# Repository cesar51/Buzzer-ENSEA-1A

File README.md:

# Buzzer-ENSEA-1A
Projet de buzzers connectés pour jeux et quiz

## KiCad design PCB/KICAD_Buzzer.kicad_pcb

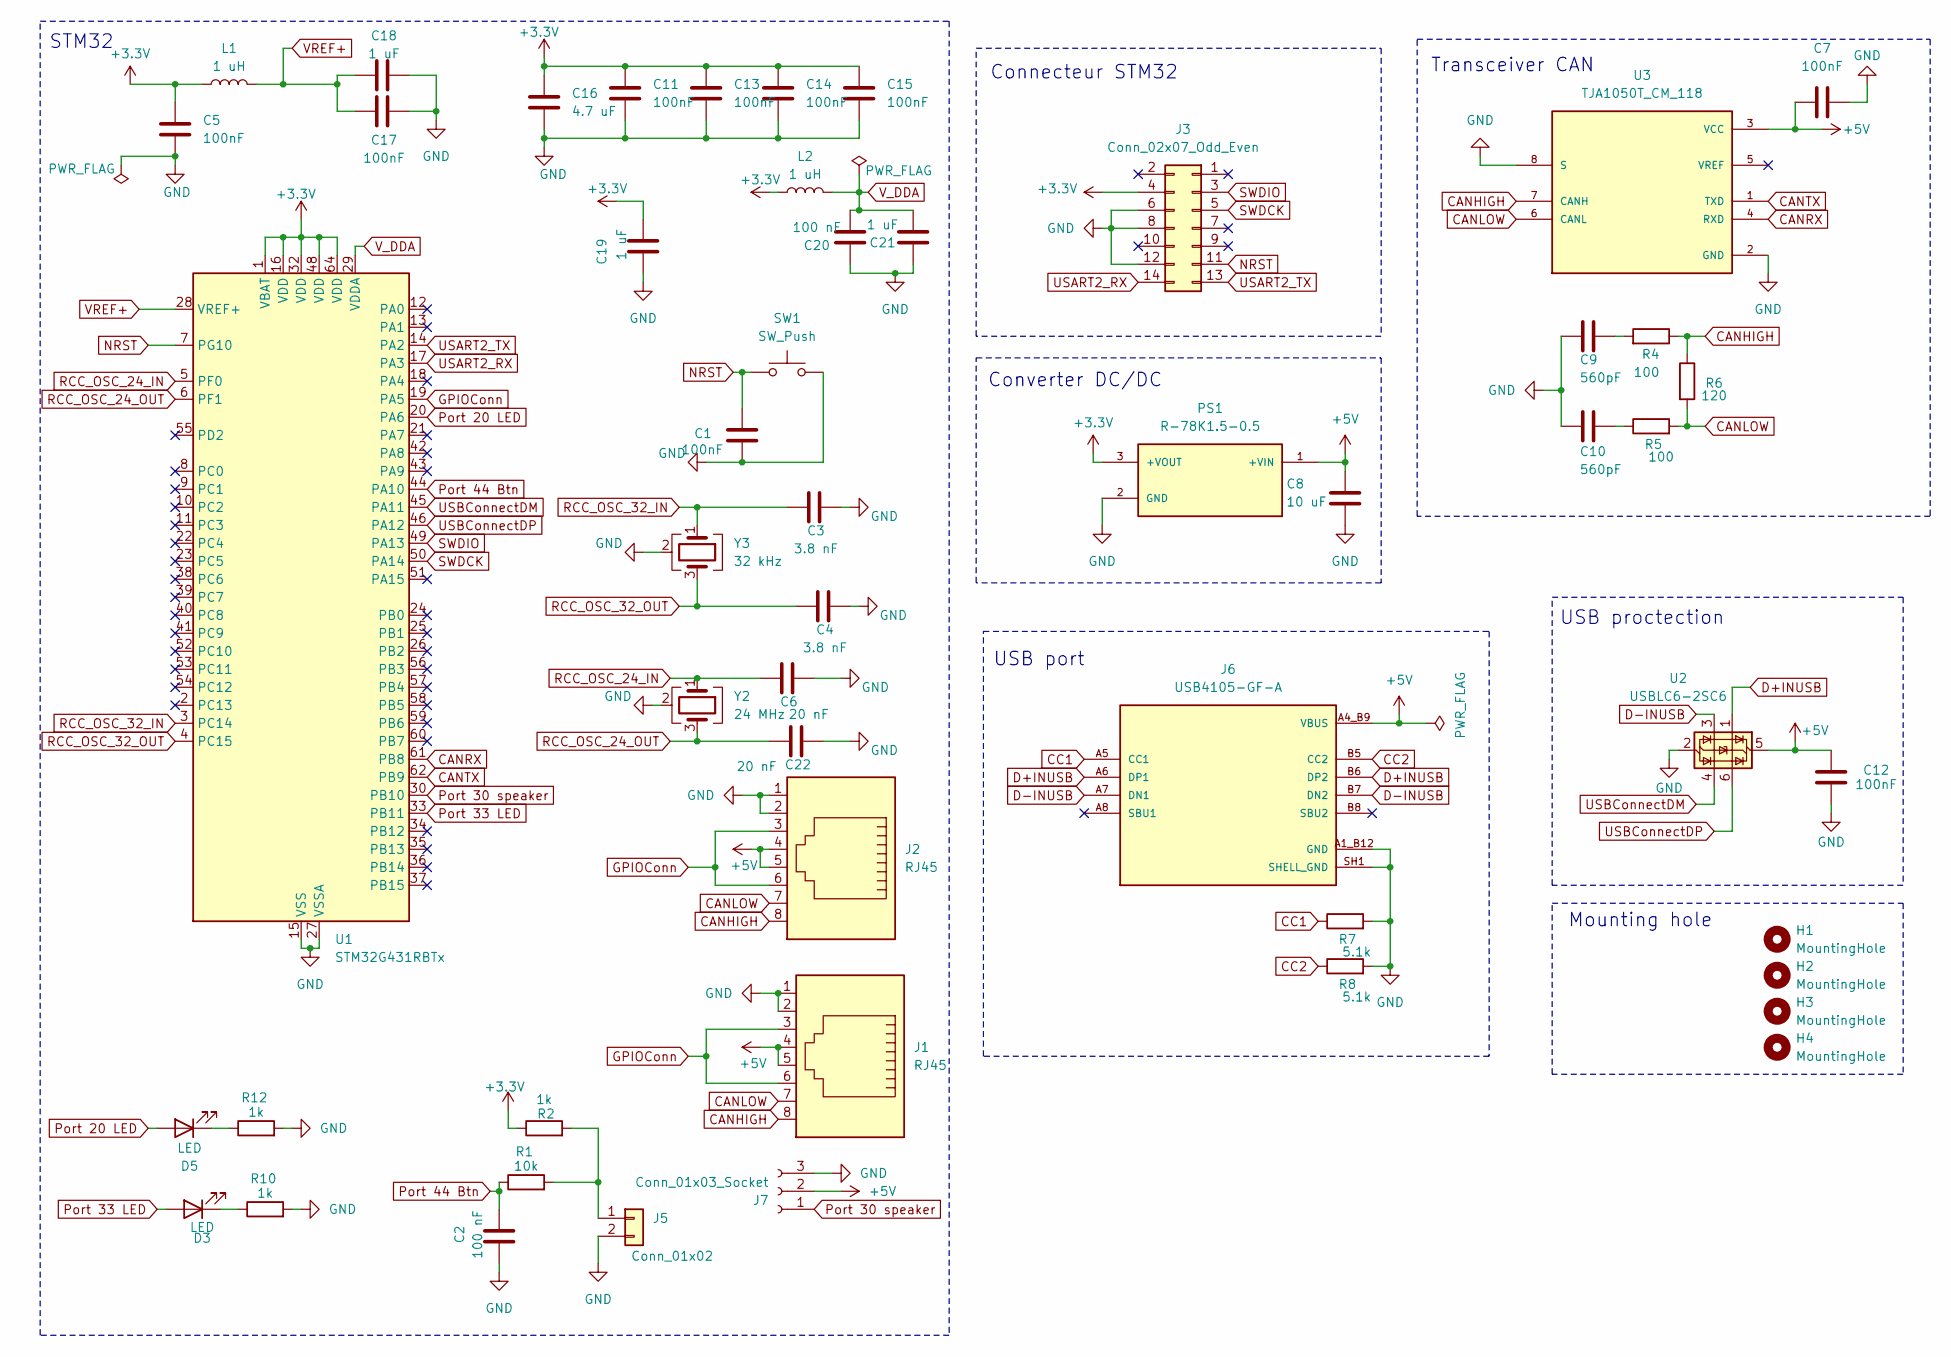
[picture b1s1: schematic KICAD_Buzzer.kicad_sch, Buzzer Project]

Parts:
C1, C5, C7, C11, C12, C13, C14, C15, C17: 100nF; C_0603_1608Metric_Pad1.08x0.95mm_HandSolder
C2, C20: 100 nF; C_0603_1608Metric_Pad1.08x0.95mm_HandSolder
C3, C4: 3.8 nF; C_0603_1608Metric_Pad1.08x0.95mm_HandSolder
C6, C22: 20 nF; C_0603_1608Metric_Pad1.08x0.95mm_HandSolder
C8: 10 uF; C_0603_1608Metric_Pad1.08x0.95mm_HandSolder
C9, C10: 560pF; C_0603_1608Metric_Pad1.08x0.95mm_HandSolder
C16: 4.7 uF; C_0603_1608Metric_Pad1.08x0.95mm_HandSolder
C18, C19, C21: 1 uF; C_0603_1608Metric_Pad1.08x0.95mm_HandSolder
D3, D5: LED; LED_PLCC_2835
H1, H2, H3, H4: MountingHole; MountingHole_3.2mm_M3_DIN965_Pad
J1, J2: RJ45; RJ45_Amphenol_54602-x08_Horizontal
J3: Conn_02x07_Odd_Even; PinHeader_2x07_P1.27mm_Vertical_SMD
J5: Conn_01x02; PinSocket_1x02_P2.54mm_Vertical
J6: USB4105-GF-A; GCT_USB4105-GF-A; PARTREV B4
J7: Conn_01x03_Socket; PinSocket_1x03_P2.54mm_Vertical
L1, L2: 1 uH; L_0805_2012Metric_Pad1.05x1.20mm_HandSolder
PS1: R-78K1.5-0.5; CONV_R-78K1.5-0.5; PARTREV 0/2023
R1: 10k; R_0805_2012Metric_Pad1.20x1.40mm_HandSolder
R2, R10, R12: 1k; R_0805_2012Metric_Pad1.20x1.40mm_HandSolder
R4, R5: 100; R_0805_2012Metric_Pad1.20x1.40mm_HandSolder
R6: 120; R_0805_2012Metric_Pad1.20x1.40mm_HandSolder
R7, R8: 5.1k; R_0805_2012Metric_Pad1.20x1.40mm_HandSolder
SW1: SW_Push; SW_Push_1P1T_NO_Vertical_Wuerth_434133025816
U1: STM32G431RBTx; LQFP-64_10x10mm_P0.5mm
U2: USBLC6-2SC6; SOT-23-6
U3: TJA1050T_CM_118; SOIC127P600X175-8N; PARTREV 4
Y2: 24 MHz; Crystal_SMD_2520-4Pin_2.5x2.0mm
Y3: 32 kHz; Crystal_SMD_1210-4Pin_1.2x1.0mm

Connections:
+3.3V: C5.1, C11.1, C13.1, C14.1, C15.1, C16.1, C19.2, J3.4, L1.1, L2.1, PS1.3 (+VOUT), R2.1, U1.1 (VBAT), U1.16 (VDD), U1.32 (VDD), U1.48 (VDD), U1.64 (VDD)
+5V: C7.1, C8.2, C12.1, J1.4, J1.5, J2.4, J2.5, J6.A4_B9 (VBUS), J6.B4_A9 (VBUS), J7.2, PS1.1 (+VIN), U2.5 (VBUS), U3.3 (VCC)
CANHIGH: J1.8, J2.8, R4.1, R6.1, U3.7 (CANH)
CANLOW: J1.7, J2.7, R5.2, R6.2, U3.6 (CANL)
CANRX: U1.61 (PB8), U3.4 (RXD)
CANTX: U1.62 (PB9), U3.1 (TXD)
CC1: J6.A5 (CC1), R7.1
CC2: J6.B5 (CC2), R8.1
D+INUSB: J6.A6 (DP1), J6.B6 (DP2), U2.1 (I/O1)
D-INUSB: J6.A7 (DN1), J6.B7 (DN2), U2.3 (I/O2)
GND: C1.2, C2.1, C3.1, C4.1, C5.2, C6.1, C7.2, C8.1, C9.2, C10.2, C11.2, C12.2, C13.2, C14.2, C15.2, C16.2, C17.2, C18.2, C19.1, C20.1, C21.1, C22.1, J1.1, J1.2, J2.1, J2.2, J3.6, J3.8, J3.12, J5.2, J6.A1_B12 (GND), J6.B1_A12 (GND), J6.SH1 (SHELL_GND), J6.SH2 (SHELL_GND), J6.SH3 (SHELL_GND), J6.SH4 (SHELL_GND), J7.3, PS1.2 (GND), R7.2, R8.2, R10.2, R12.2, SW1.2, U1.15 (VSS), U1.27 (VSSA), U1.31 (VSS), U1.47 (VSS), U1.63 (VSS), U2.2 (GND), U3.2 (GND), U3.8 (S), Y2.2 (G), Y2.4 (G), Y3.2 (G), Y3.4 (G)
GPIOConn: J1.3, J1.6, J2.3, J2.6, U1.19 (PA5)
NRST: C1.1, J3.11, SW1.1, U1.7 (PG10)
unnamed: C9.1, R4.2
unnamed: C10.1, R5.1
unnamed: D3.1 (K), R10.1
unnamed: D5.1 (K), R12.1
unnamed: J5.1, R1.2, R2.2
Port 20 LED: D5.2 (A), U1.20 (PA6)
Port 30 speaker: J7.1, U1.30 (PB10)
Port 33 LED: D3.2 (A), U1.33 (PB11)
Port 44 Btn: C2.2, R1.1, U1.44 (PA10)
RCC_OSC_24_IN: C6.2, U1.5 (PF0), Y2.1
RCC_OSC_24_OUT: C22.2, U1.6 (PF1), Y2.3
RCC_OSC_32_IN: C3.2, U1.3 (PC14), Y3.1
RCC_OSC_32_OUT: C4.2, U1.4 (PC15), Y3.3
SWDCK: J3.5, U1.50 (PA14)
SWDIO: J3.3, U1.49 (PA13)
USART2_RX: J3.14, U1.17 (PA3)
USART2_TX: J3.13, U1.14 (PA2)
USBConnectDM: U1.45 (PA11), U2.4 (I/O2)
USBConnectDP: U1.46 (PA12), U2.6 (I/O1)
VREF+: C17.1, C18.1, L1.2, U1.28 (VREF+)
V_DDA: C20.2, C21.2, L2.2, U1.29 (VDDA)

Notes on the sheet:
USB proctection
Transceiver CAN
Mounting hole
STM32
USB port
Connecteur STM32
Converter DC/DC

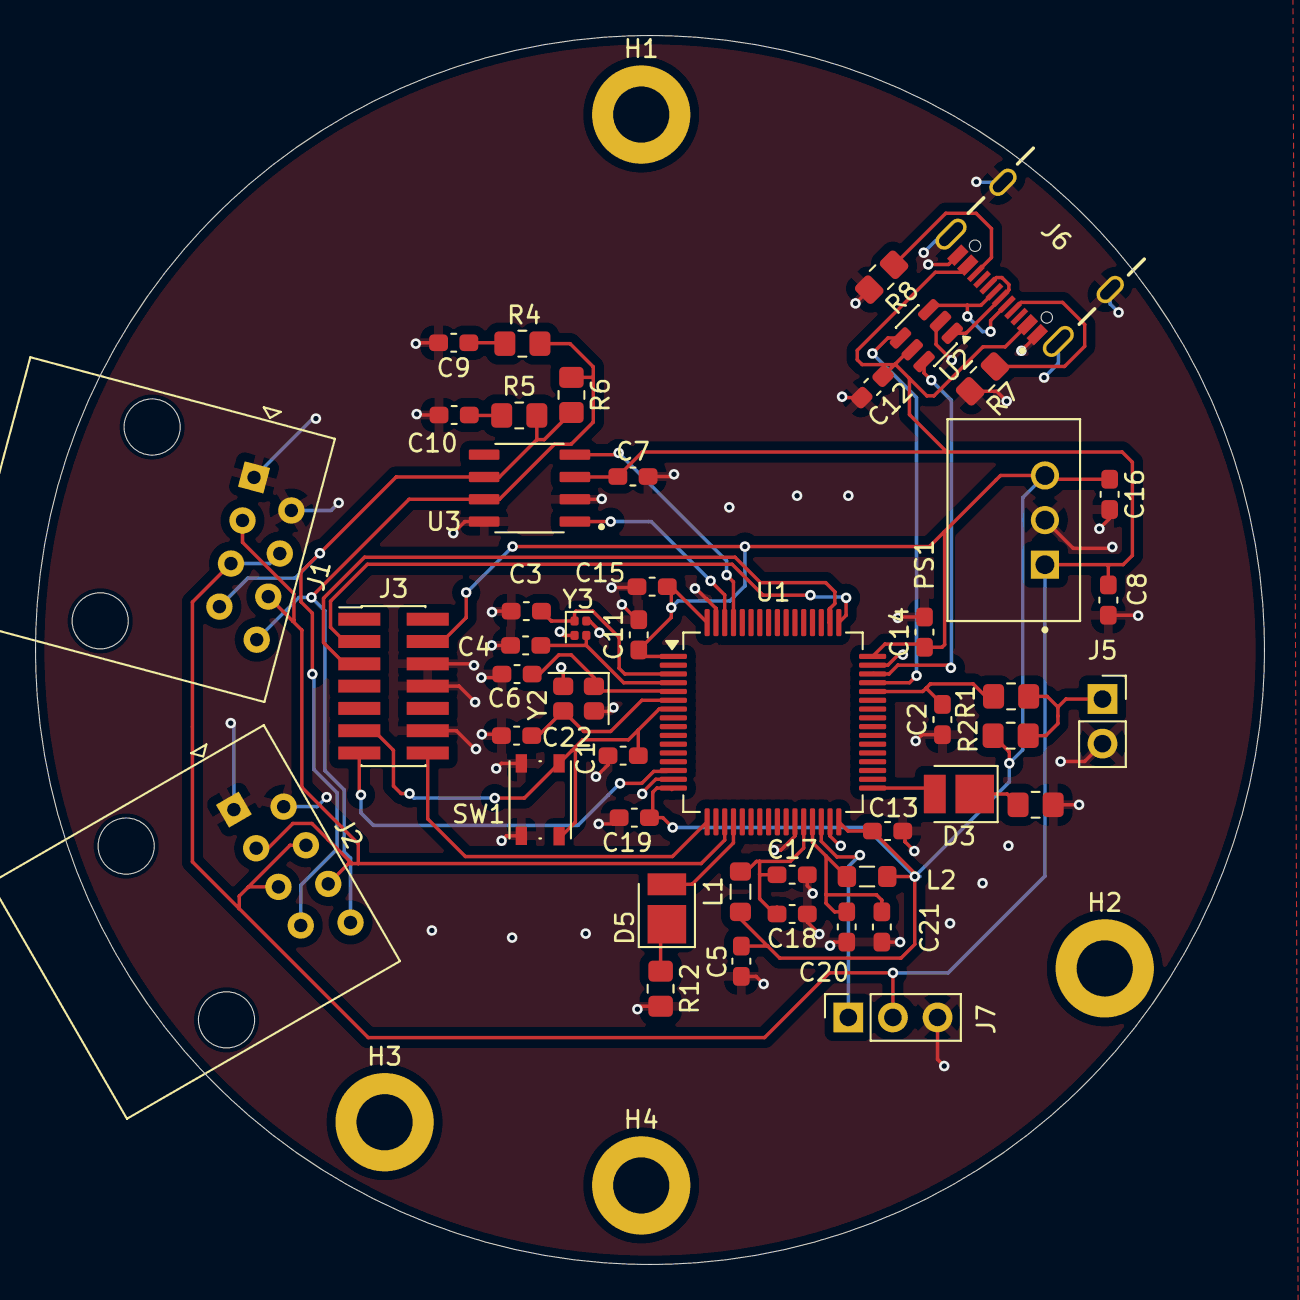
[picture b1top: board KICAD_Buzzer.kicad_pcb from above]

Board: 2 copper layers, 70.0 x 70.0 mm, 52 parts (0 on the bottom side), 34 nets.

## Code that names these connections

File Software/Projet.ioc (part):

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Mcu.Name=STM32G431R(6-8-B)Tx
Mcu.Package=LQFP64
Mcu.UserName=STM32G431RBTx
PA10.GPIOParameters=GPIO_Label
PA10.GPIO_Label=Bouton_Joueur
PA10.Signal=GPIO_Input
PA11.Mode=Device
PA11.Signal=USB_DM
PA12.Mode=Device
PA12.Signal=USB_DP
PA13.Mode=Serial_Wire
PA13.Signal=SYS_JTMS-SWDIO
PA14.Mode=Serial_Wire
PA14.Signal=SYS_JTCK-SWCLK
PA2.Mode=Asynchronous
PA2.Signal=USART2_TX
PA3.Mode=Asynchronous
PA3.Signal=USART2_RX
PA5.GPIOParameters=GPIO_Label
PA5.GPIO_Label=GPIOConn
PA5.Signal=GPIO_Output
PA6.GPIOParameters=GPIO_Label
PA6.GPIO_Label=LED_1
PA6.Signal=GPIO_Output
PB10.GPIOParameters=GPIO_Label
PB10.GPIO_Label=Speaker
PB10.Signal=GPIO_Output
PB11.GPIOParameters=GPIO_Label
PB11.GPIO_Label=LED_2
PB11.Signal=GPIO_Output
PB8-BOOT0.Mode=FDCAN_Activate
PB8-BOOT0.Signal=FDCAN1_RX
PB9.Mode=FDCAN_Activate
PB9.Signal=FDCAN1_TX
PC14-OSC32_IN.Mode=LSE-External-Oscillator
PC14-OSC32_IN.Signal=RCC_OSC32_IN
PC15-OSC32_OUT.Mode=LSE-External-Oscillator
PC15-OSC32_OUT.Signal=RCC_OSC32_OUT
PF0-OSC_IN.Mode=HSE-External-Oscillator
PF0-OSC_IN.Signal=RCC_OSC_IN
PF1-OSC_OUT.Mode=HSE-External-Oscillator
PF1-OSC_OUT.Signal=RCC_OSC_OUT
RCC.HSE_VALUE=8000000
RCC.SYSCLKFreq_VALUE=16000000
board=custom

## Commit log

2026-05-24 import
2026-05-24 Create dk
2026-05-24 ajout software
